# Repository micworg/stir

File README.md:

# Dual magnetic stir controller V2

## Overview

This is the Arduino project to build a double magnetic stirrer based on 2 fans, a 1602 LCD display, a KY-040 encoder and an Arduino Nano and a special PCB designed in the Hobbybrauer-Forum.

V2 supports dual voltage for the fans which increases the speed range.

In order to put the stirrer into operation you have to change the settings in stir.ino according to your setup (see below).

The stir V2 software is compatible with V1 hardware if you have used neither the RS232 Api nor the OFF0 and OFF1 relais pins.

## Part List

* 1x PCB "Stir V2.0"
* 1x Arduino Nano V3
* 1x [Voltage regulator TE818 5-24V to 5V 3A step down buck converter](https://www.ebay.de/itm/5x-Voltage-Regulator-5-24V-to-5V-3A-Step-Down-Buck-Converter-Power-Module-TE818/133109140535?ssPageName=STRK%3AMEBIDX%3AIT&_trksid=p2057872.m2749.l2649)
* 2x [Relais Omron G5Q-1-EU 5DC switching printrelais 5 V/DC 5A](https://www.conrad.de/de/p/omron-g5q-1-eu-5dc-printrelais-5-v-dc-5-a-1-wechsler-1-st-503930.html)
* 2x [Diode 1N4148 Diotec](https://www.conrad.de/de/p/stmicroelectronics-schottky-diode-gleichrichter-1n5822-do-201ad-40-v-einzeln-168275.html)
* 1x [Electrolytic capacitor 1000µF/16V Yageo SE016M1000B5S-1015](https://www.conrad.de/de/p/yageo-se016m1000b5s-1015-elektrolyt-kondensator-radial-bedrahtet-5-mm-1000-f-16-v-20-x-h-10-mm-x-15-mm-1-st-445386.html)
* 2x [Diode 1N5822 STMicroelectronics Schottky-Diode](https://www.conrad.de/de/p/diotec-ultraschnelle-si-diode-1n4148-sod-27-75-v-150-ma-162280.html)
* 4x [Metal film resistor 10 KOhm 0,6 W](https://www.conrad.de/de/p/rs-pro-metallschichtwiderstand-10k-0-5-0-6w-807200469.html)
* 2x Fan BeQuiet SilentWings 3 120mm PWM Highspeed or Noctua NF-R8 Redux-1800 80mm PWM
* 1x Power supply 12V-16V DC / 2A
* 1x Built-in socket for plug-in power supply unit
* 1x I2C 16x2 Arduino LCD Display Module
* 1x [Rotary encoder KY-040](https://www.conrad.de/de/p/joy-it-kodierter-drehschalter-rotary-encoder-1695709.html)
* 2x Magnet mount (3D printed)
* 4x Neodymium magnet 20x10 mm (N52, 1 oder 2 mm dick)

In addition, a housing is required that can be individually designed according to possibilities and capabilities.

## Reference

This project was created based on an idea from the german Hobbybrauer-Forum and would not be possible without the ideas from there.

The forum: https://hobbybrauer.de/

The thread: https://hobbybrauer.de/forum/viewtopic.php?f=21&t=1456

Special thanks for development and testing:

* Herbert Schmid 
* Adrian Sigel
* Jens Warkentin
* Bastian Werner

## Overview of Functions

All functions are controlled by the KY-040 encoder:

* **Short Press:** change between menu, stirrer 1 and stirrer 2
* **Turn when menu is selected**: change between menu items (SPEED, BOOST, BTIME, CATCH, CTIME)
* **Long press when menu is selected**: lock all functions (unlock also by long press)
* **When a stirrer is selected**:
  * **SPEED**: turn sets speed, long press switches stirrer on or off.
  * **BOOST**: turn sets boost speed, long press activates/deactivates the boost function (running time is shown in the display).
  * **BTIME**: turn changes the boost time in minutes.
  * **CATCH**: turn activates/deactivates the fishing function
  * **CTIME**: turn changes the interval in minutes for the fish catching function
  * **RTIME**: turn changes speed rise time in seconds (applies to power on, stirrer on, boost on and fish catching)
  * **OTIME**: turn changes switch off time in hours (the timer activates immediately, 0 = switch off disabled)
  * **RNVAL**: random value range (a random values in this range will be added to speed) 
* **Other menu options**:
  * **CFG**: Configuration menu 

Functions in the congirutation sub menu
* **Short Press**: switch between config option and and value.
* **Long press**: exit configuration menu.
* **Turn**: select configuration option or change value.

## Display Indicators:

* **Bottom Left**: Menu
* **Bottom Center/Right**: displays the set values for the stirrers depending on the selected menu item.
* **Top Center/Right**: displays the current stirrer speed (or 'OFF' or 'CAT' (Fishing)).
* **Top Left**: shows the remaining time of the boost or switch off function.

## Settings (in stir.ino)

|Value|Config|Description|
|:----------------|:-----|:----------|
|`LGHT`           |`LGHT`|LCD display brightness|
|`SPEEDINC1`      |`SPI1`|increment of speed values when turning the encoder (1. range)|
|`SPEEDINC2`      |`SPI2`|increment of speed values when turning the encoder (2. range)|
|`SPEEDINC3`      |`SPI3`|increment of speed values when turning the encoder (3. range)|
|`SPEEDSTEP1`     |`SPS1`|speed increment steps (increment changes at these values, separates range 1 and 2)|
|`SPEEDSTEP2`     |`SPS2`|speed increment steps (increment changes at these values, separates range 2 and 3))|
|`FANMIN`         |`FMIN`|fan minimum speed (should be a value at which the fan runs safely) (rpm)|
|`FANMAX`         |`FMAX`|fan maximum speed  (it's important that this is the real maximum value of the fan) (rpm)|
|`FANINIT`        |`FINI`|set fans to high voltage for 3 sec at boot (0/1)|
|`BOFF`           |`BOFF`|if set boost off will also turn the normal mode off (0/1)|
|`BINC`           |`BINC`|boost time increment (min)|
|`CINC`           |`CINC`|catch time increment (min)|
|`RINC`           |`RINC`|rise time increment (sec)|
|`OINC`           |`OINC`|off timer increment (hour)|
|`RNDINC`         |`RINC`|randon value increment (rpm)|
|`CATCHSTOP`      |`CSTP`|stop interval for stir fish catch function (ms)|
|`PWM0`, `PWM1`   |      |PWM output pins for fan speed|
|`PWM2`           |      |PWM output pin for LCD brightness control|
|`I0`, `I1`       |      |interrupts for rpm measurement (0/1 for Uno/Nano, 2/3 for Leonardo/ProMicro)|
|`SWAPENC`        |`SWEN`|switch KY-040 encoder direxction (0/1)| 
|`CLK`, `DT`, `SW`|      |pins for KY-040 encoder| 
|`R0`, `R0`       |      |voltage select relais pin| 
|`RTHRES`         |`RTHR`|voltage switch threshold (rpm)| 
|`RINTERVAL`      |`XINT`|regulation interval (ms)|
|`RDELAY`         |`XDEL`|extra regulation delay when value changes (ms)|
|`RTOL`           |`XTOL`|regulation tolerance (rpm)|
|`RNDINTERVL`     |`RINT`|randon value range change interval (ms)|
|`SINTERVAL`      |`SINT`|speed measurement interval (ms)|
|`SAVERAGE`       |`SAVG`|speed measurement average|
|`SAVETAG`        |      |parameter save identifier|
|`SAVEDELAY`      |      |delay in seconds before parameter will be saved to EEPROM|
|`LCDB`           |      |LCD brightness steps (10 values, 0=off, 255=max)|
|`RESET`          |`RSET`|change this value in configuration menu to 1 for factory reset|

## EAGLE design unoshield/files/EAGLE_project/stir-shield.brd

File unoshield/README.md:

# Stir Shield

Stir shield for Arduino UNO from Adrian Sigel.

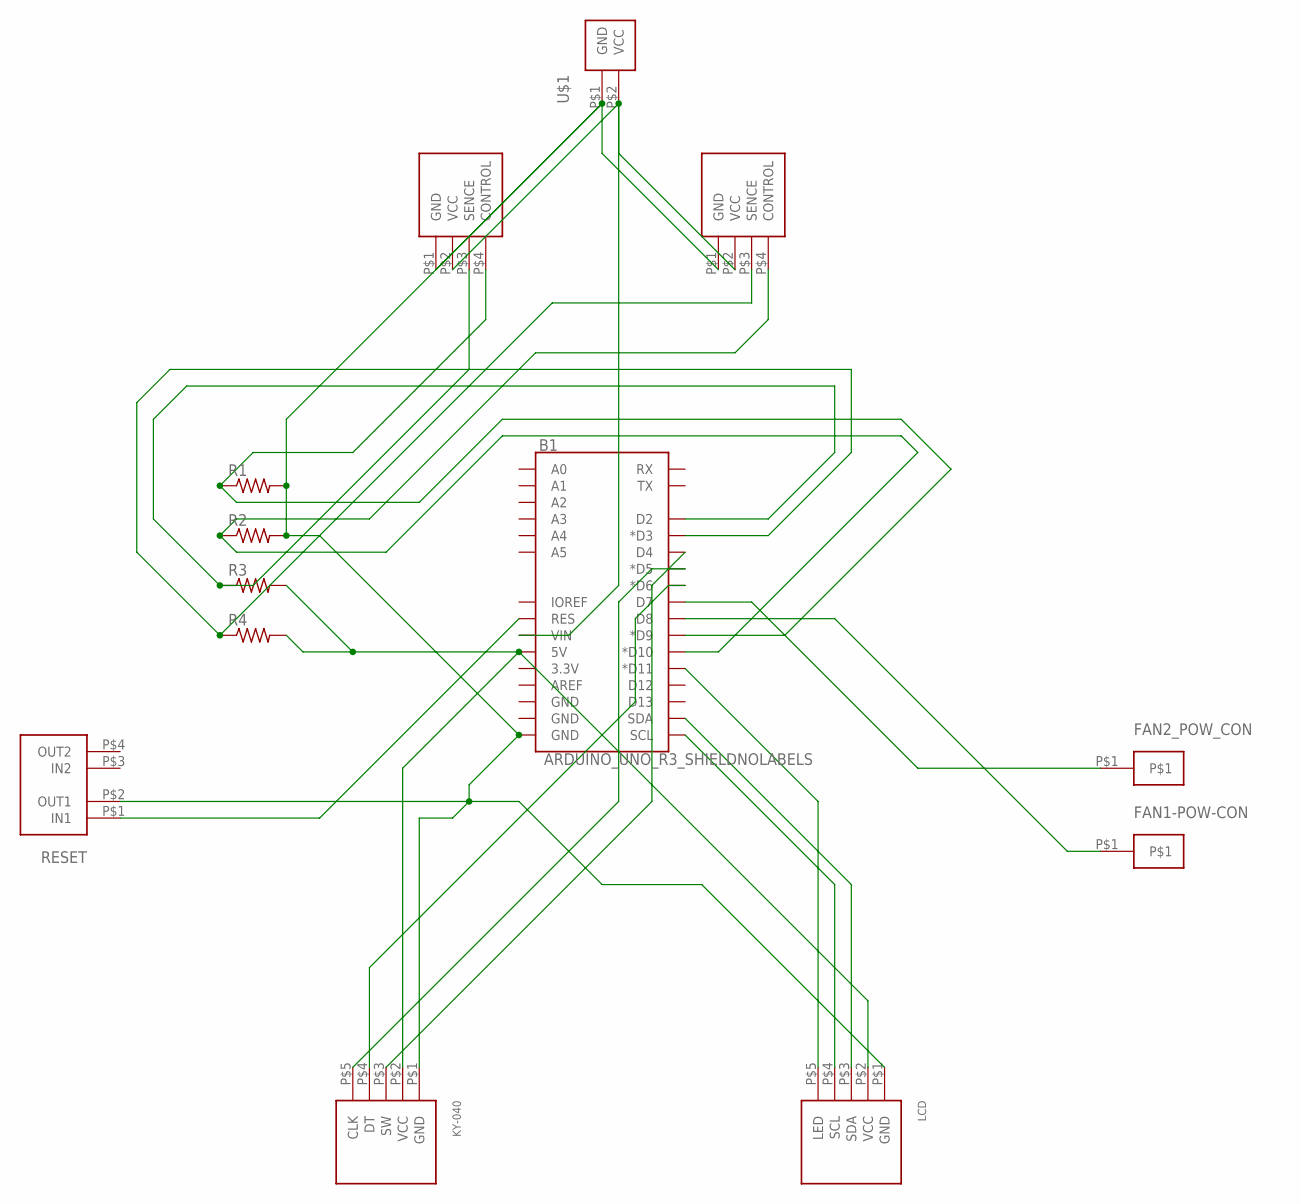
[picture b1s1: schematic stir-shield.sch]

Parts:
B1: ARDUINO_UNO_R3_SHIELDNOLABELS; UNO_R3_SHIELD_NOLABELS
FAN1, FAN2: 4PIN
FAN1-POW-CON, FAN2_POW_CON: 1PIN
KY-040: 5PIN_KY-04
LCD: 5PIN_LCD
R1, R2, R3, R4: FLIPFLOP-RES; 0805-THM
RESET: BUTTON
U$1: 2PIN

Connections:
unnamed: B1.D8, FAN1-POW-CON.P$1
unnamed: B1.VIN, FAN1.P$2 (VCC), FAN2.P$2 (VCC), U$1.P$2 (VCC)
unnamed: B1.D9 (*D9), FAN1.P$4 (CONTROL), R1.1
unnamed: B1.D10 (*D10), FAN2.P$4 (CONTROL), R2.1
unnamed: B1.5V, KY-040.P$2 (VCC), LCD.P$2 (VCC), R3.2, R4.2
unnamed: B1.D2, FAN1.P$3 (SENCE), R3.1
unnamed: B1.D3 (*D3), FAN2.P$3 (SENCE), R4.1
unnamed: B1.D11 (*D11), LCD.P$5 (LED)
unnamed: B1.D7, FAN2_POW_CON.P$1
unnamed: B1.SCL, LCD.P$4 (SCL)
unnamed: B1.SDA, LCD.P$3 (SDA)
unnamed: B1.D4, KY-040.P$3 (SW)
unnamed: B1.D6 (*D6), KY-040.P$4 (DT)
unnamed: B1.D5 (*D5), KY-040.P$5 (CLK)
unnamed: B1.GND@0 (GND), FAN1.P$1 (GND), FAN2.P$1 (GND), KY-040.P$1 (GND), LCD.P$1 (GND), R1.2, R2.2, RESET.P$2 (OUT1), U$1.P$1 (GND)
RESET: B1.RES, RESET.P$1 (IN1)

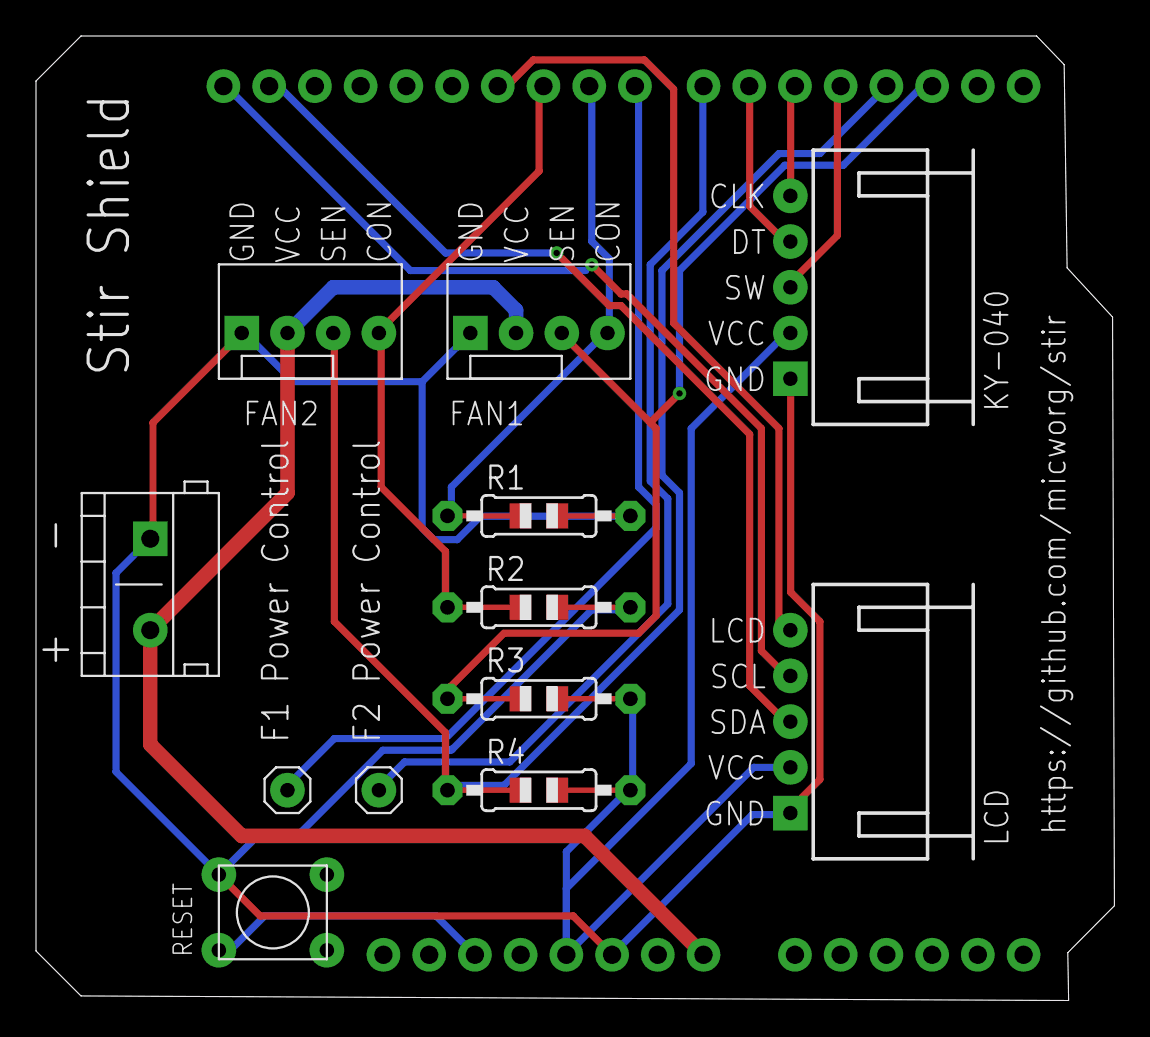
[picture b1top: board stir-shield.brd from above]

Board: 2 copper layers, 59.9 x 53.6 mm, 13 parts (0 on the bottom side), 16 nets.

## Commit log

2019-02-20 updated schematics
2019-02-21 code cleanup, better regulation
2019-02-21 code cleanup, bug fixes
2019-02-22 added cad files
2019-02-25 new release, v.1.3.0
2019-02-26 various changes and additions
2019-02-26 bug fix
2019-03-04 bug fixes, updated cad file
2019-03-06 1.4.0
2019-03-09 code cleanup, bug fixes, API
2019-03-09 minor changes, bug fixes
2019-03-11 added switch off timer, bug fixes
2019-03-13 minor changes
2019-03-15 updated comment
2019-03-20 minor changes, updated readme
2019-03-20 image updated, updated readme
2019-03-20 libraries added
2019-03-29 off state pins, brightness control
2019-04-30 added case files from Jens
2019-04-30 reordered CAD directory
2019-04-30 added bezel files from Herbert
2019-04-30 added Magnetrührer_Folie.pdf
2019-05-12 added UNO shield
2019-06-02 random mode added
2019-07-07 improved encoder behavior
2019-09-12 added nanoshiel
2019-09-12 added NANO shield
2019-09-17 updated cad files
2019-09-18 updated NANO shields
2019-09-28 updated support files
2020-03-12 added links for components

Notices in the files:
parts and their libraries:
SparkFun-Boards: Licensing: Creative Commons ShareAlike 4.0 International - https://creativecommons.org/licenses/by-sa/4.0
